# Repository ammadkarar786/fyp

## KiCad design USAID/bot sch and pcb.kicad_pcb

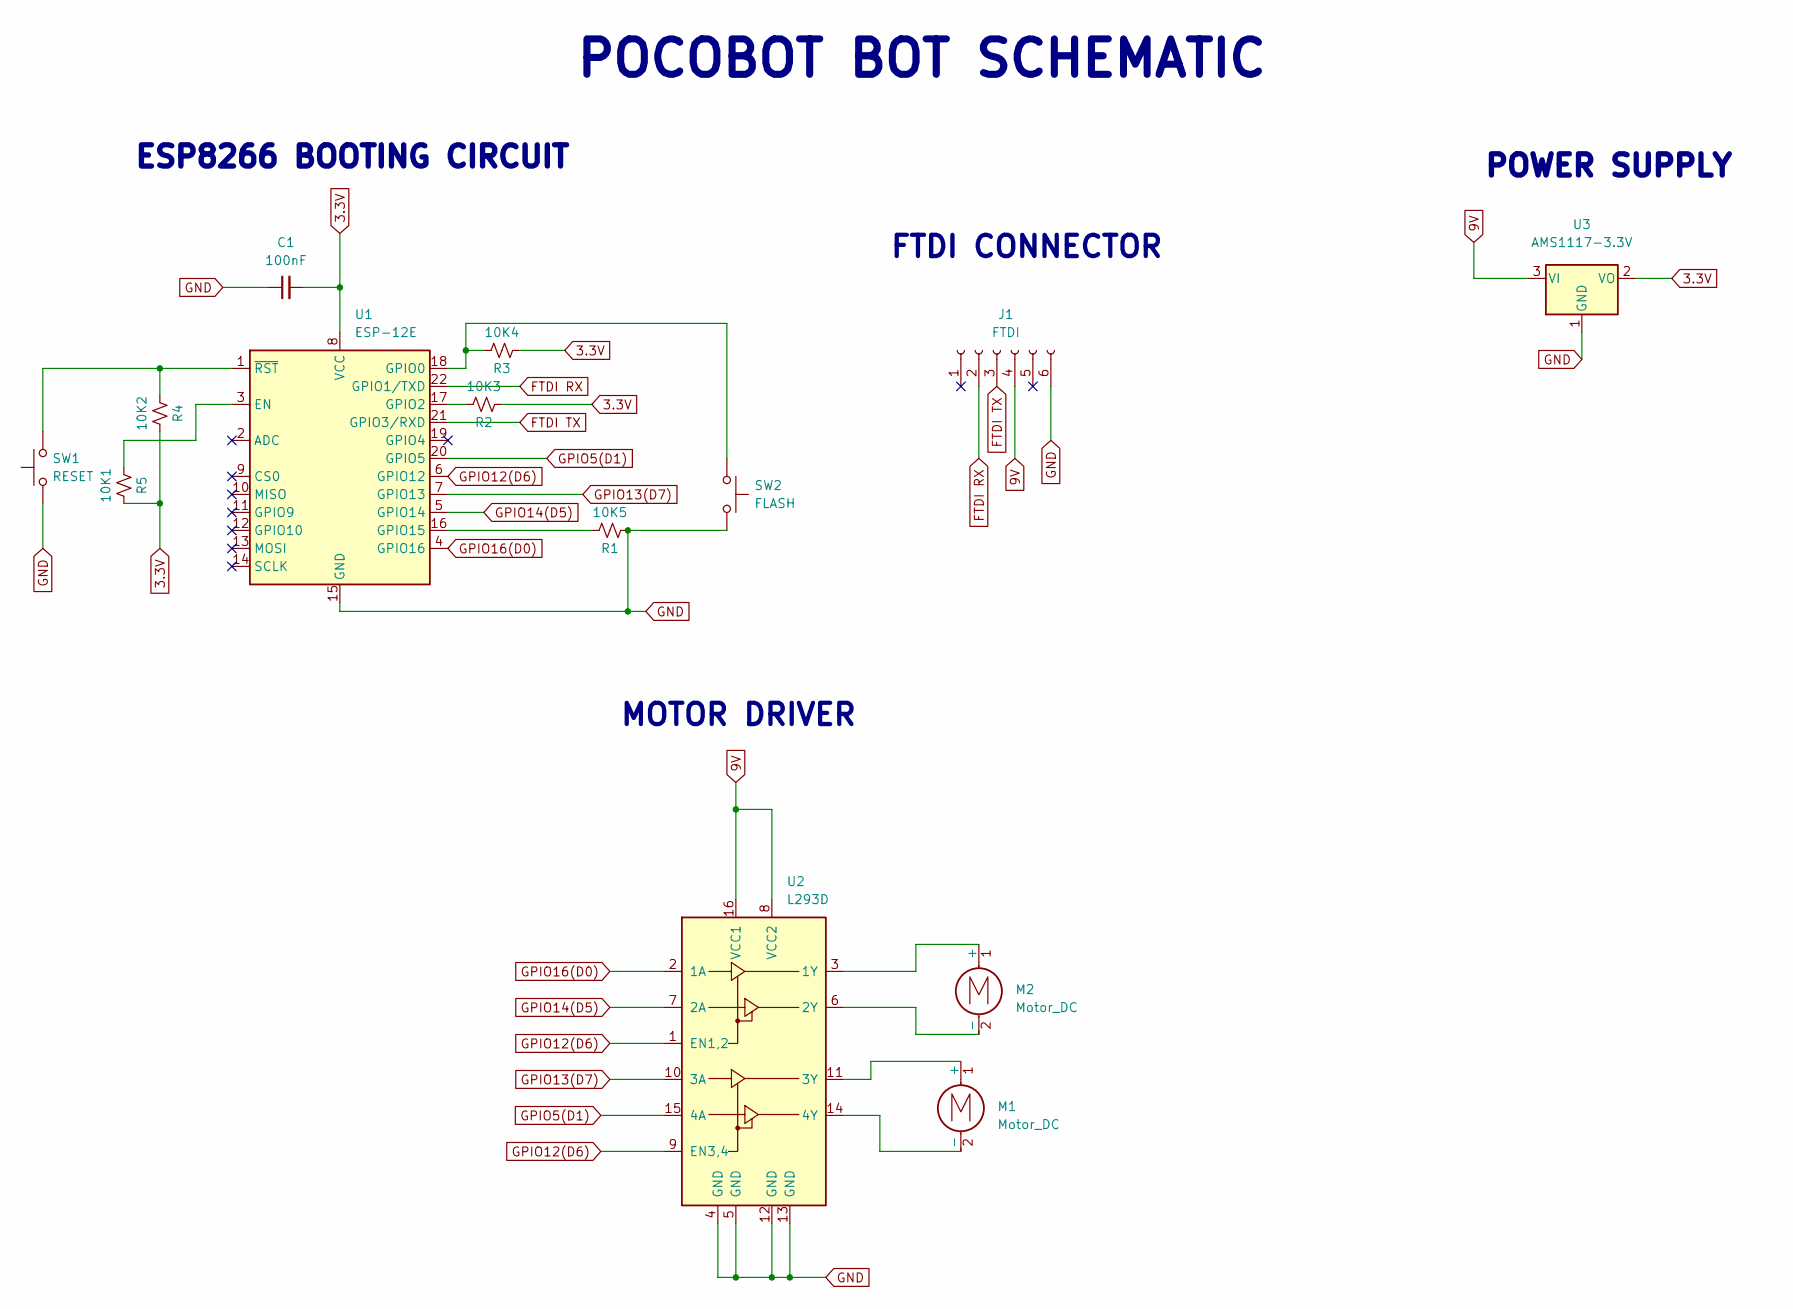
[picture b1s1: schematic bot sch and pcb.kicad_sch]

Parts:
10K1: R5; R_0805_2012Metric
10K2: R4; R_0805_2012Metric
10K3: R2; R_0805_2012Metric
10K4: R3; R_0805_2012Metric
10K5: R1; R_0805_2012Metric
C1: 100nF; C_0805_2012Metric
J1: FTDI; JST_EH_S6B-EH_1x06_P2.50mm_Horizontal
M1, M2: Motor_DC; TerminalBlock_4Ucon_1x02_P3.50mm_Horizontal
SW1: RESET; SW_SPST_Omron_B3FS-105xP
SW2: FLASH; SW_SPST_Omron_B3FS-105xP
U1: ESP-12E
U2: L293D; DIP-16_W7.62mm
U3: AMS1117-3.3V; SOT-223-3_TabPin2

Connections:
3.3V: 10K1.1, 10K2.1, 10K3.2, 10K4.2, C1.2, U1.8 (VCC), U3.2 (VO)
9V: J1.4, U2.8 (VCC2), U2.16 (VCC1), U3.3 (VI)
FTDI RX: J1.2, U1.22 (GPIO1/TXD)
FTDI TX: J1.3, U1.21 (GPIO3/RXD)
GND: 10K5.2, C1.1, J1.6, SW1.1 (A), SW1.2 (A), SW2.3 (B), SW2.4 (B), U1.15 (GND), U2.4 (GND), U2.5 (GND), U2.12 (GND), U2.13 (GND), U3.1 (GND)
GPIO5(D1): U1.20 (GPIO5), U2.15 (4A)
GPIO12(D6): U1.6 (GPIO12), U2.1 (EN1,2), U2.9 (EN3,4)
GPIO13(D7): U1.7 (GPIO13), U2.10 (3A)
GPIO14(D5): U1.5 (GPIO14), U2.7 (2A)
GPIO16(D0): U1.4 (GPIO16), U2.2 (1A)
unnamed: 10K1.2, U1.3 (EN)
unnamed: 10K2.2, SW1.3 (B), SW1.4 (B), U1.1 (~RST)
unnamed: 10K3.1, U1.17 (GPIO2)
unnamed: 10K4.1, SW2.1 (A), SW2.2 (A), U1.18 (GPIO0)
unnamed: 10K5.1, U1.16 (GPIO15)
unnamed: M1.1 (+), U2.11 (3Y)
unnamed: M1.2 (-), U2.14 (4Y)
unnamed: M2.1 (+), U2.3 (1Y)
unnamed: M2.2 (-), U2.6 (2Y)

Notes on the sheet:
POWER SUPPLY
FTDI CONNECTOR
MOTOR DRIVER
POCOBOT BOT SCHEMATIC
ESP8266 BOOTING CIRCUIT

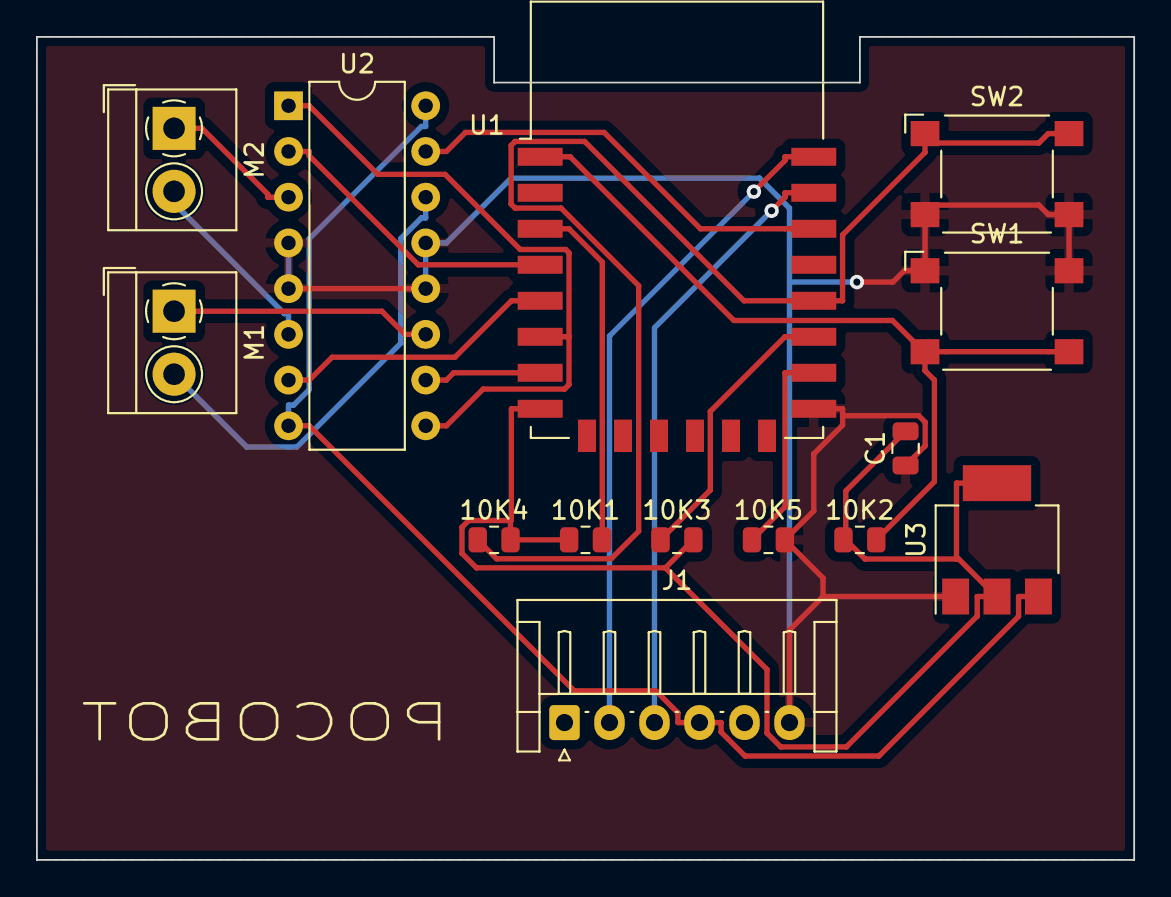
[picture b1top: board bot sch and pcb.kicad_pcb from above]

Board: 2 copper layers, 61.0 x 45.7 mm, 14 parts (0 on the bottom side), 19 nets.

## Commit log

2021-12-08 motor driver done
2021-12-08 INTERFACE BOARD SET
2021-12-10 pocobot in working condition
2021-12-11 array change to 16
2021-12-14 Create Yousuf786
2021-12-15 setting
2022-01-11 pcb materia upload
2022-01-11 pcb material update
2022-01-16 FILE CHK
2022-01-16 all the testing done
    time speed all set
2022-01-16 MULTIPLEXER SCHEMATIC
2022-01-16 CHECK KICAD
2022-01-16 USAID SCH DONE
    BOT
2022-01-16 BOOT LOAD CKT
2022-01-16 I/O NAMES CHANGE
2022-01-16 delete
2022-01-16 HEADINGS
2022-01-16 pad sample edited
2022-01-16 Revert "update"
    This reverts commit 1eaf0319fb1fe428aa7ac6962f796e9fe74e652f, reversing
    changes made to ee1dee68ccab3115c0157bff6e2ade1fa99c5460.
2022-01-16 created backup
2022-01-16 16 PADS ADDED
2022-01-16 3 IN 1
2022-01-16 CORRECT ERRORS
    FTDI CONNECTION FIXED INTERFACE BOARD CONNECTION CHECK
2022-01-16 SCHMETIC COMPLETE FOR INTERFACE BOARD
2022-01-16 HEADING ADDED
2022-01-16 INTERFACE BOARD PDF COMPLETE
2022-01-16 BOT SCHEMATIC COMPLETED
2022-01-18 demo
2022-01-19 ALLIGNMENTS
2022-03-14 file rearrange
2022-03-14 test
2022-03-14 filler added
2022-03-19 python gui testing done
2022-03-19 document save
2022-03-21 yousuf
2022-03-21 Create .~lock.FORTINITE REPORT.docx#
2022-03-24 half done with painter
2022-03-28 gui and AI gesture done
2022-04-22 rasberry pi backup
2022-05-11 checking
2022-05-13 TESTING DONE
2022-05-21 FINAL SPEED TESTING
2022-05-29 values change
2022-05-31 maria task
2022-06-01 deleted
2022-06-02 block diagram
2022-07-12 commited
2022-07-31 ultrasonic upload
    ultrasonic upload
2022-07-31 ir done
